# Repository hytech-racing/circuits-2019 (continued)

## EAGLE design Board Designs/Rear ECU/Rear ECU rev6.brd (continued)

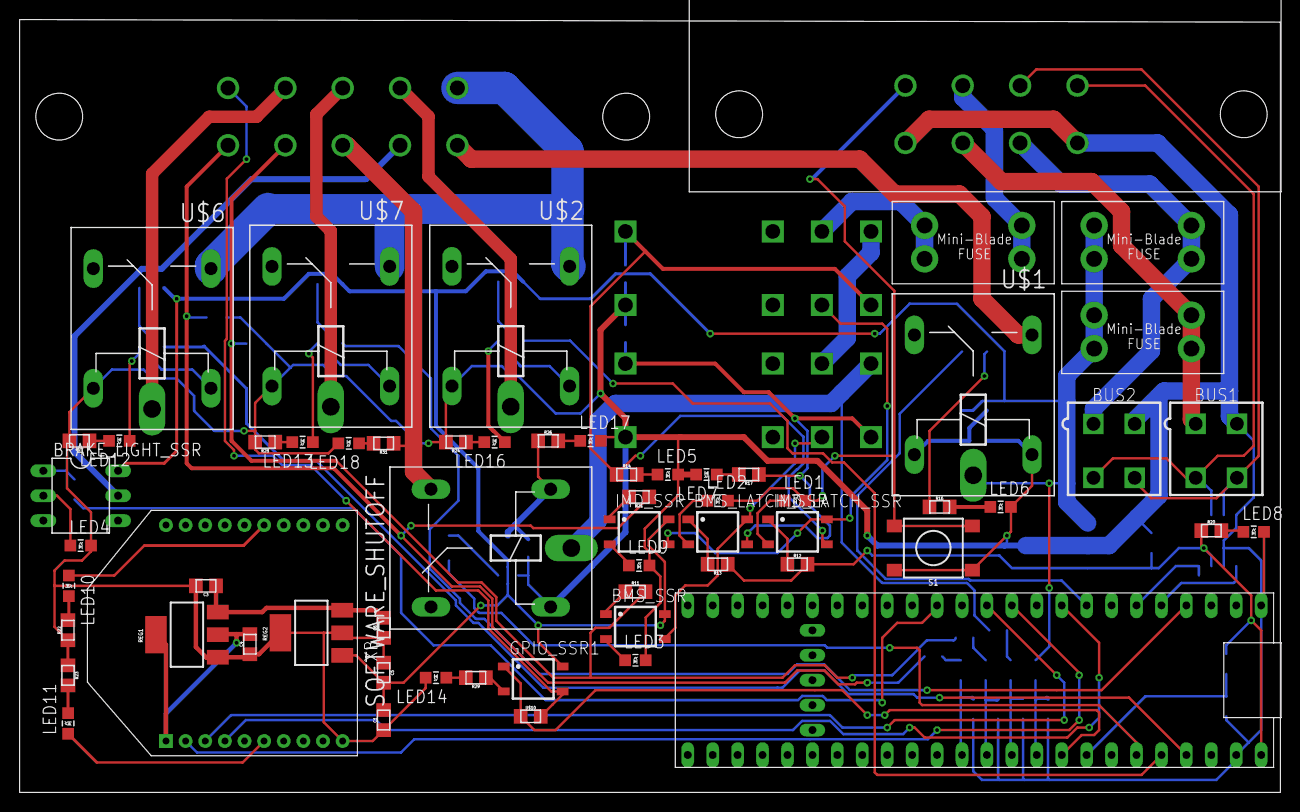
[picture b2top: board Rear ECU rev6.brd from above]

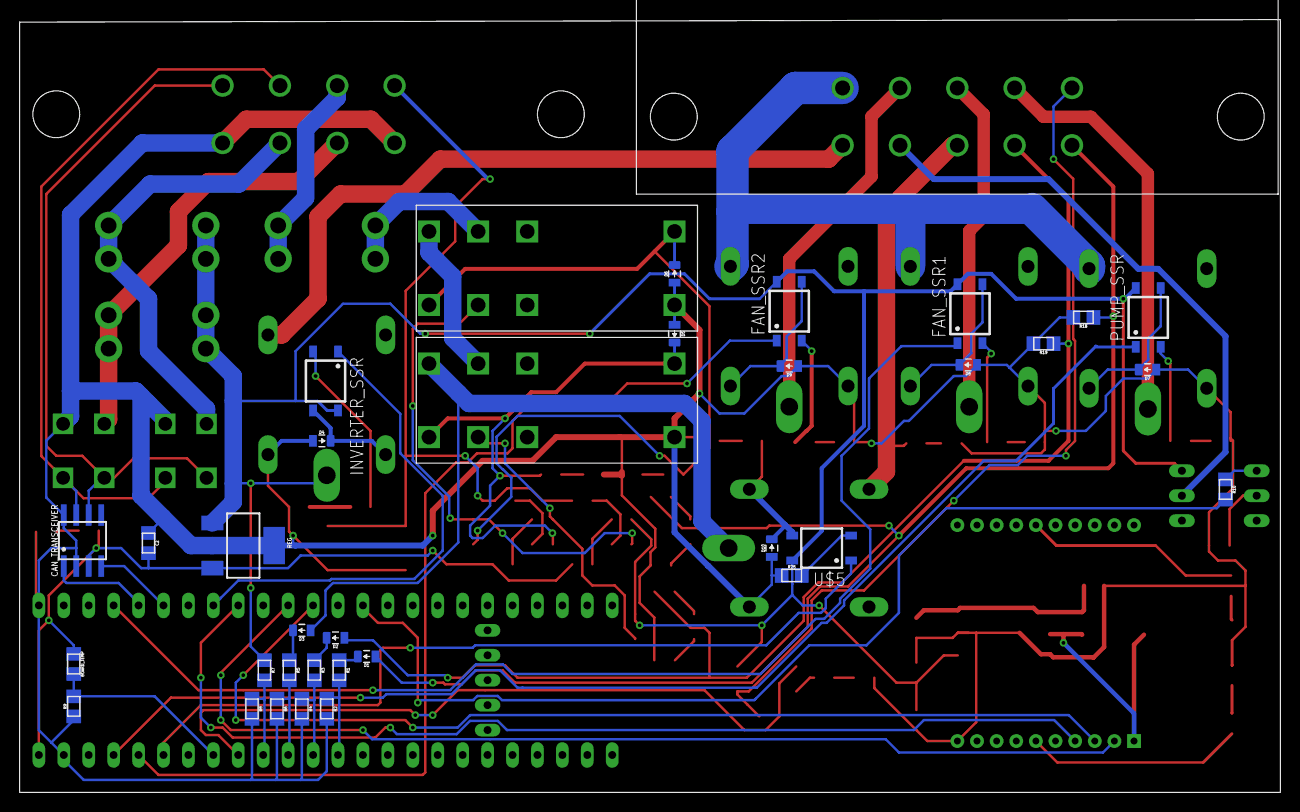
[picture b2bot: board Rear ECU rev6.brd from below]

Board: 2 copper layers, 128.4 x 78.7 mm, 96 parts (35 on the bottom side), 83 nets.

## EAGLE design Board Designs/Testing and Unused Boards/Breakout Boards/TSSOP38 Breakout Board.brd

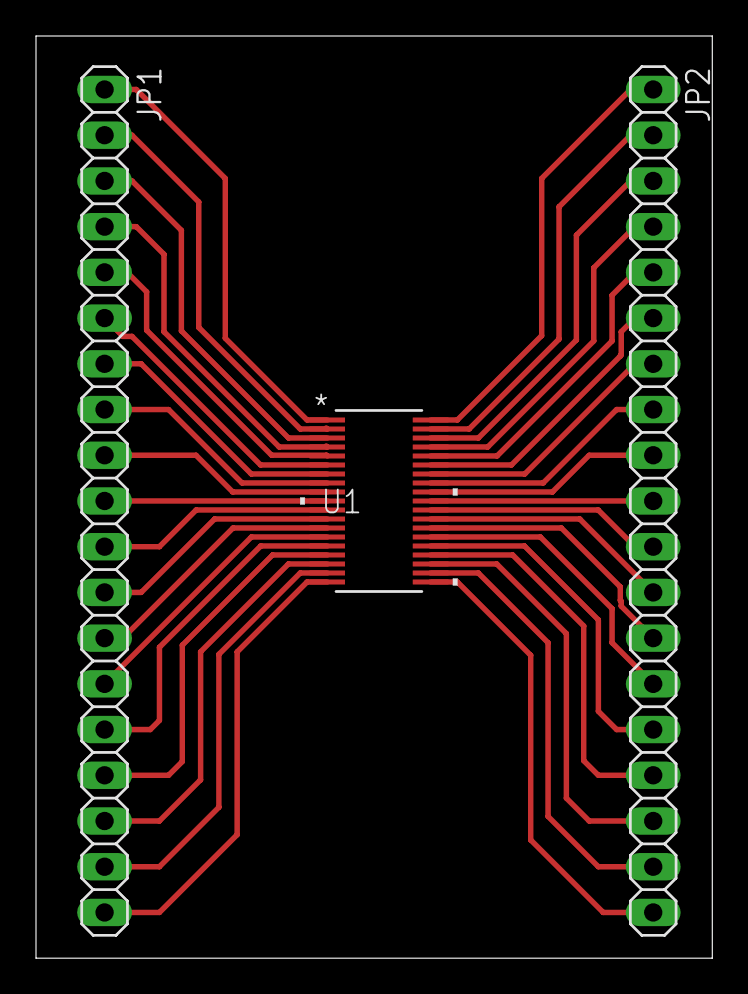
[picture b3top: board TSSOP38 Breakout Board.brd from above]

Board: 2 copper layers, 37.6 x 51.2 mm, 3 parts (0 on the bottom side), 38 nets.

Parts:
JP1, JP2: 1X19
U1: ADS7952SDBTDBT38-M; DBT38-M

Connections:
unnamed: JP1.1, U1.1
unnamed: JP1.2, U1.2
unnamed: JP1.3, U1.3
unnamed: JP1.4, U1.4
unnamed: JP1.5, U1.5
unnamed: JP1.6, U1.6
unnamed: JP1.7, U1.7
unnamed: JP1.8, U1.8
unnamed: JP1.19, U1.19
unnamed: JP1.18, U1.18
unnamed: JP1.17, U1.17
unnamed: JP1.16, U1.16
unnamed: JP1.15, U1.15
unnamed: JP1.14, U1.14
unnamed: JP1.13, U1.13
unnamed: JP1.12, U1.12
unnamed: JP1.11, U1.11
unnamed: JP1.10, U1.10
unnamed: JP1.9, U1.9
unnamed: JP2.1, U1.38
unnamed: JP2.2, U1.37
unnamed: JP2.3, U1.36
unnamed: JP2.4, U1.35
unnamed: JP2.5, U1.34
unnamed: JP2.6, U1.33
unnamed: JP2.7, U1.32
unnamed: JP2.8, U1.31
unnamed: JP2.9, U1.30
unnamed: JP2.10, U1.29
unnamed: JP2.11, U1.28
unnamed: JP2.12, U1.27
unnamed: JP2.13, U1.26
unnamed: JP2.14, U1.25
unnamed: JP2.15, U1.24
unnamed: JP2.16, U1.23
unnamed: JP2.17, U1.22
unnamed: JP2.18, U1.21
unnamed: JP2.19, U1.20

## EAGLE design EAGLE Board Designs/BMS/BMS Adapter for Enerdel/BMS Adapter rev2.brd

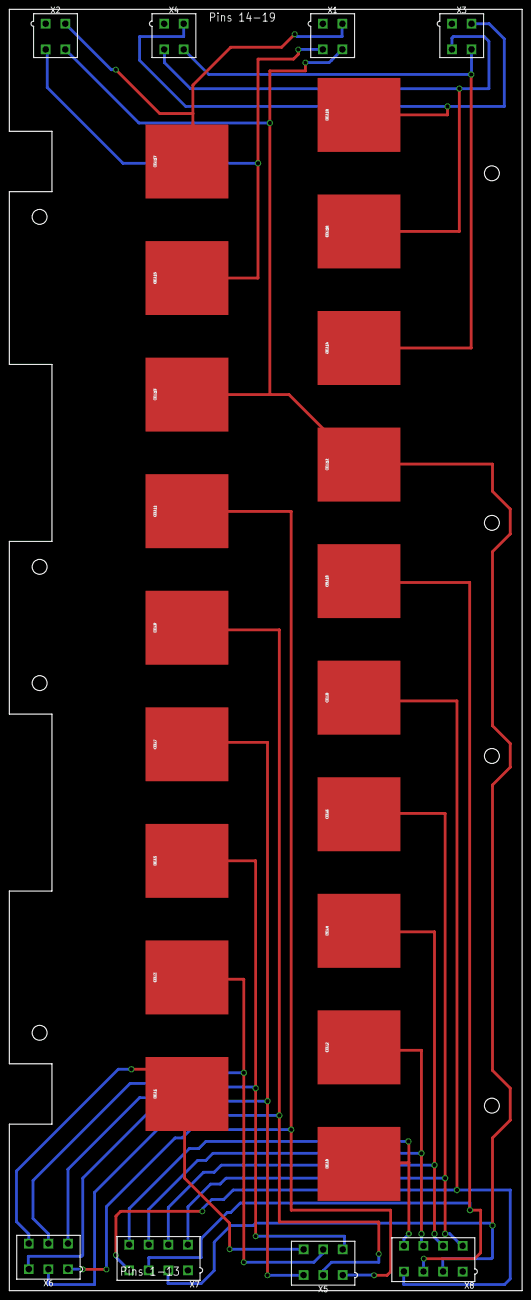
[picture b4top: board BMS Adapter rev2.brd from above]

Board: 2 copper layers, 110.0 x 274.8 mm, 27 parts (0 on the bottom side), 18 nets.

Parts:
CELL0, CELL1, CELL2, CELL3, CELL4, CELL5, CELL6, CELL7, CELL8, CELL9, CELL10, CELL11, CELL12, CELL13, CELL14, CELL15, CELL16, CELL17, CELL18: BATTERY_SPRING_KEYSTONE5222; KEYSTONE5222
X1, X2, X3, X4: CONNECTOR-4; MINIFIT_5566-4
X5, X6: CONNECTOR-6; MINIFIT_5566-6
X7, X8: CONNECTOR-8; MINIFIT_5566-8

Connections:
CELL0: CELL0.P$1, X7.8, X8.8
CELL1: CELL1.P$1, X5.6, X6.6
CELL2: CELL2.P$1, X7.7, X8.7
CELL3: CELL3.P$1, X5.5, X6.5
CELL4: CELL4.P$1, X7.6, X8.6
CELL5: CELL5.P$1, X5.4, X6.4
CELL6: CELL6.P$1, X7.5, X8.5
CELL7: CELL7.P$1, X5.3, X6.3
CELL8: CELL8.P$1, X7.4, X8.4
CELL9: CELL9.P$1, X5.2, X6.2
CELL10: CELL10.P$1, X7.3, X8.3
CELL11: CELL11.P$1, X5.1, X6.1
CELL12: CELL12.P$1, CELL13.P$1, X1.4, X2.4, X7.2, X8.2
CELL14: CELL14.P$1, X3.4, X4.4
CELL15: CELL15.P$1, X1.3, X2.3
CELL16: CELL16.P$1, X3.3, X4.3
CELL17: CELL17.P$1, X1.2, X2.2
CELL18: CELL18.P$1, X3.2, X4.2

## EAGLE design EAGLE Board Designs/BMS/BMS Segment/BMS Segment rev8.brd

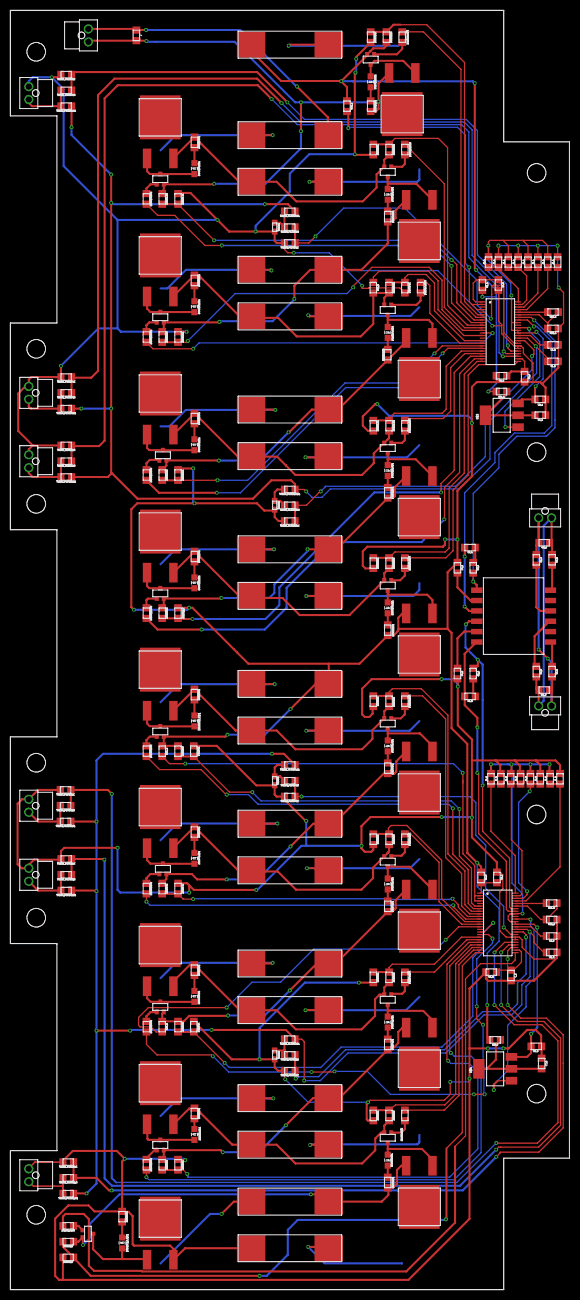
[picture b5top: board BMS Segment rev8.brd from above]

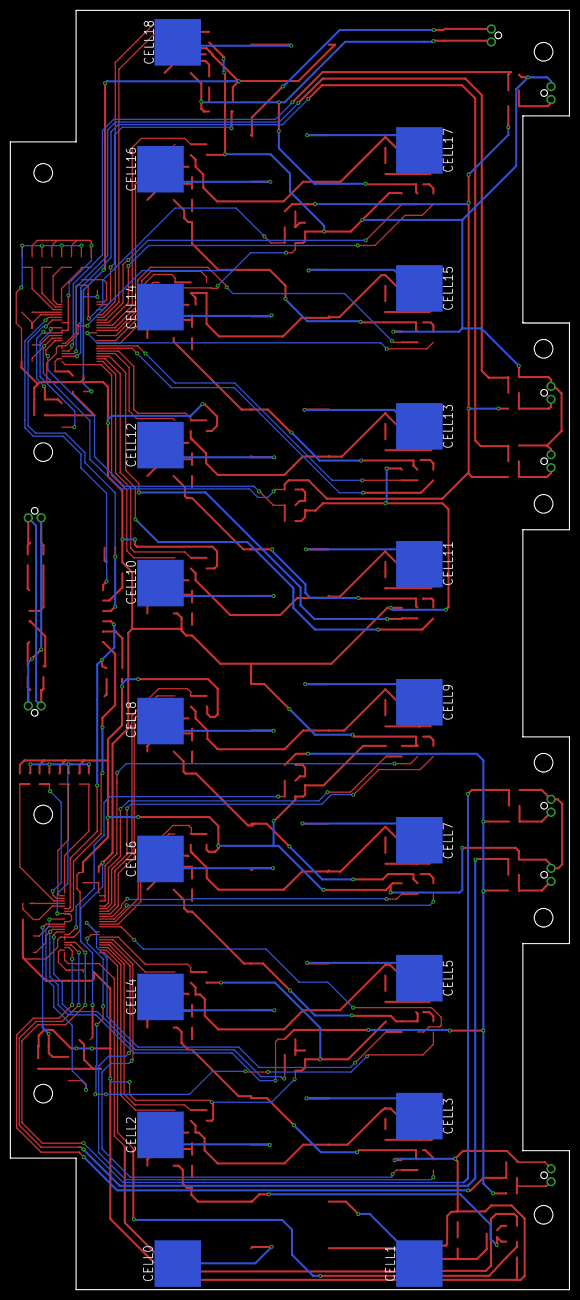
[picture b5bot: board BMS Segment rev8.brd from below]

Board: 2 copper layers, 108.0 x 247.1 mm, 267 parts (19 on the bottom side), 193 nets.

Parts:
AMS_TEST_PORT1: CONNECTOR-2NANO-FIT_VERTICAL-2; NANO-FIT_VERTICAL-2
C1_A, C1_B, C2_A, C2_B, C8_A, C8_B: 1uF; 0805
C3_A, C3_B: 15pF; 0805
C4_A, C4_B, C5_A: 10nF; 0805
C6_A, C6_B, C7_A, C7_B: 0.1uF; 0805
CELL0, CELL1, CELL2, CELL3, CELL4, CELL5, CELL6, CELL7, CELL8, CELL9, CELL10, CELL11, CELL12, CELL13, CELL14, CELL15, CELL16, CELL17, CELL18: BATTERY_SPRING; KEYSTONE5203
C_5: 10nF; 0805
DRAIN1:C, DRAIN2:C, DRAIN3:C, DRAIN4:C, DRAIN5:C, DRAIN6:C, DRAIN7:C, DRAIN8:C, DRAIN9:C, DRAIN10:C, DRAIN11:C, DRAIN12:C, DRAIN13:C, DRAIN14:C, DRAIN15:C, DRAIN16:C, DRAIN17:C, DRAIN18:C: 10nF; 0805
DRAIN1:DISCHARGE, DRAIN2:DISCHARGE, DRAIN3:DISCHARGE, DRAIN4:DISCHARGE, DRAIN5:DISCHARGE, DRAIN6:DISCHARGE, DRAIN7:DISCHARGE, DRAIN8:DISCHARGE, DRAIN9:DISCHARGE, DRAIN10:DISCHARGE, DRAIN11:DISCHARGE, DRAIN12:DISCHARGE, DRAIN13:DISCHARGE, DRAIN14:DISCHARGE, DRAIN15:DISCHARGE, DRAIN16:DISCHARGE, DRAIN17:DISCHARGE, DRAIN18:DISCHARGE: 5R; PWR163
DRAIN1:GATE, DRAIN2:GATE, DRAIN3:GATE, DRAIN4:GATE, DRAIN5:GATE, DRAIN6:GATE, DRAIN7:GATE, DRAIN8:GATE, DRAIN9:GATE, DRAIN10:GATE, DRAIN11:GATE, DRAIN12:GATE, DRAIN13:GATE, DRAIN14:GATE, DRAIN15:GATE, DRAIN16:GATE, DRAIN17:GATE, DRAIN18:GATE: 3K3; 0805
DRAIN1:LED1, DRAIN2:LED1, DRAIN3:LED1, DRAIN4:LED1, DRAIN5:LED1, DRAIN6:LED1, DRAIN7:LED1, DRAIN8:LED1, DRAIN9:LED1, DRAIN10:LED1, DRAIN11:LED1, DRAIN12:LED1, DRAIN13:LED1, DRAIN14:LED1, DRAIN15:LED1, DRAIN16:LED1, DRAIN17:LED1, DRAIN18:LED1: RED; LED-805
DRAIN1:PFET, DRAIN2:PFET, DRAIN3:PFET, DRAIN4:PFET, DRAIN5:PFET, DRAIN6:PFET, DRAIN7:PFET, DRAIN8:PFET, DRAIN9:PFET, DRAIN10:PFET, DRAIN11:PFET, DRAIN12:PFET, DRAIN13:PFET, DRAIN14:PFET, DRAIN15:PFET, DRAIN16:PFET, DRAIN17:PFET, DRAIN18:PFET: P-CHANNEL_MOSFET_DMP3099L-7; SOT23
DRAIN1:R, DRAIN2:R, DRAIN3:R, DRAIN4:R, DRAIN5:R, DRAIN6:R, DRAIN7:R, DRAIN8:R, DRAIN9:R, DRAIN10:R, DRAIN11:R, DRAIN12:R, DRAIN13:R, DRAIN14:R, DRAIN15:R, DRAIN16:R, DRAIN17:R, DRAIN18:R: 100R; 0805
DRAIN1:R1, DRAIN2:R1, DRAIN3:R1, DRAIN4:R1, DRAIN5:R1, DRAIN6:R1, DRAIN7:R1, DRAIN8:R1, DRAIN9:R1, DRAIN10:R1, DRAIN11:R1, DRAIN12:R1, DRAIN13:R1, DRAIN14:R1, DRAIN15:R1, DRAIN16:R1, DRAIN17:R1, DRAIN18:R1: 150R; 0805
F0, F1, F2, F3, F4, F5, F6, F7, F8, F9, F10, F11, F12, F13, F14, F15, F16, F17, F18: 0001.2704.11; 5X20MM_FUSE
ISOSPI_A: CONNECTOR-2NANO-FIT_VERTICAL-2; NANO-FIT_VERTICAL-2
ISOSPI_B: CONNECTOR-2NANO-FIT_VERTICAL-2; NANO-FIT_VERTICAL-2
J, J1_A, J1_B, J2_A, J2_B, J3_A, J3_B, J4_A, J4_B, J5_A, J5_B, J6_A, J6_B, J7_A, J7_B, J8_A, J8_B: 0805
R1_A, R1_B, R2_A, R2_B: 100R; 0805
R3_A, R3_B: 402R; 0805
R4_A, R4_B, R5_A, R5_B: 22R; 0805
RB1_A, RB1_B: 1K2; 0805
RB2_A, RB2_B: 800R; 0805
RIN_A: 100R; 0805
RIN_B: 100R; 0805
RM_A: 100R; 0805
RM_B: 100R; 0805
RU1_A, RU1_B: 100R; 0805
RU2_A, RU2_B: 100Ω; 0805
THERM1, THERM2, THERM3, THERM4: 10K; 0603
THERM1_A, THERM1_B, THERM2_A, THERM2_B, THERM3_A, THERM3_B: Th1; NANO-FIT_VERTICAL-2
THERM_FILTER1:C, THERM_FILTER2:C, THERM_FILTER3:C, THERM_FILTER4:C, THERM_FILTER5:C, THERM_FILTER6:C, THERM_FILTER7:C, THERM_FILTER8:C, THERM_FILTER9:C, THERM_FILTER10:C: 10nF; 0805
THERM_FILTER1:R, THERM_FILTER2:R, THERM_FILTER3:R, THERM_FILTER4:R, THERM_FILTER5:R, THERM_FILTER6:R, THERM_FILTER7:R, THERM_FILTER8:R, THERM_FILTER9:R, THERM_FILTER10:R: 100R; 0805
THERM_FILTER1:R1, THERM_FILTER2:R1, THERM_FILTER3:R1, THERM_FILTER4:R1, THERM_FILTER5:R1, THERM_FILTER6:R1, THERM_FILTER7:R1, THERM_FILTER8:R1, THERM_FILTER9:R1, THERM_FILTER10:R1: 10K; 0805
TRANSFORMER: HM2102NLT
U$1, U$2: LTC6804-2; LTC6804
U$3, U$4: SOT223

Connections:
C0_A: C5_A.1, R2_A.2, U$1.26
C0_B: C_5.1, R2_B.2, U$2.26
C1_A: DRAIN10:C.1, DRAIN10:R.2, U$1.24
C1_B: DRAIN1:C.1, DRAIN1:R.2, U$2.24
C2_A: DRAIN11:C.1, DRAIN11:R.2, U$1.22
C2_B: DRAIN2:C.1, DRAIN2:R.2, U$2.22
C3_A: DRAIN12:C.1, DRAIN12:R.2, U$1.20
C3_B: DRAIN3:C.1, DRAIN3:R.2, U$2.20
C4_A: DRAIN13:C.1, DRAIN13:R.2, U$1.18
C4_B: DRAIN4:C.1, DRAIN4:R.2, U$2.18
C5_A: DRAIN14:C.1, DRAIN14:R.2, U$1.16
C5_B: DRAIN5:C.1, DRAIN5:R.2, U$2.16
C7_A: DRAIN15:C.1, DRAIN15:R.2, U$1.12
C7_B: DRAIN6:C.1, DRAIN6:R.2, U$2.12
C8_A: DRAIN16:C.1, DRAIN16:R.2, U$1.10
C8_B: DRAIN7:C.1, DRAIN7:R.2, U$2.10
C9_A: DRAIN17:C.1, DRAIN17:R.2, U$1.8
C9_B: DRAIN8:C.1, DRAIN8:R.2, U$2.8
C10_A: DRAIN18:C.1, DRAIN18:R.2, U$1.6
C10_B: DRAIN9:C.1, DRAIN9:R.2, U$2.6
CC0: CELL0.P$1, F0.P$1
CC1: CELL1.P$1, F1.P$1
CC2: CELL2.P$1, F2.P$1
CC3: CELL3.P$1, F3.P$1
CC4: CELL4.P$1, F4.P$1
CC5: CELL5.P$1, F5.P$1
CC6: CELL6.P$1, F6.P$1
CC7: CELL7.P$1, F7.P$1
CC8: CELL8.P$1, F8.P$1
CC9: CELL9.P$1, F9.P$1
CC10: CELL10.P$1, F10.P$1
CC11: CELL11.P$1, F11.P$1
CC12: CELL12.P$1, F12.P$1
CC13: CELL13.P$1, F13.P$1
CC14: CELL14.P$1, F14.P$1
CC15: CELL15.P$1, F15.P$1
CC16: CELL16.P$1, F16.P$1
CC17: CELL17.P$1, F17.P$1
CC18: CELL18.P$1, F18.P$1
DRAIN1:GATE: DRAIN1:GATE.1, DRAIN1:PFET.1
DRAIN1:N$1: DRAIN1:DISCHARGE.1, DRAIN1:LED1.A, DRAIN1:PFET.3
DRAIN1:N$2: DRAIN1:LED1.C, DRAIN1:R1.2
DRAIN2:GATE: DRAIN2:GATE.1, DRAIN2:PFET.1
DRAIN2:N$1: DRAIN2:DISCHARGE.1, DRAIN2:LED1.A, DRAIN2:PFET.3
DRAIN2:N$2: DRAIN2:LED1.C, DRAIN2:R1.2
DRAIN3:GATE: DRAIN3:GATE.1, DRAIN3:PFET.1
DRAIN3:N$1: DRAIN3:DISCHARGE.1, DRAIN3:LED1.A, DRAIN3:PFET.3
DRAIN3:N$2: DRAIN3:LED1.C, DRAIN3:R1.2
DRAIN4:GATE: DRAIN4:GATE.1, DRAIN4:PFET.1
DRAIN4:N$1: DRAIN4:DISCHARGE.1, DRAIN4:LED1.A, DRAIN4:PFET.3
DRAIN4:N$2: DRAIN4:LED1.C, DRAIN4:R1.2
DRAIN5:GATE: DRAIN5:GATE.1, DRAIN5:PFET.1
DRAIN5:N$1: DRAIN5:DISCHARGE.1, DRAIN5:LED1.A, DRAIN5:PFET.3
DRAIN5:N$2: DRAIN5:LED1.C, DRAIN5:R1.2
DRAIN6:GATE: DRAIN6:GATE.1, DRAIN6:PFET.1
DRAIN6:N$1: DRAIN6:DISCHARGE.1, DRAIN6:LED1.A, DRAIN6:PFET.3
DRAIN6:N$2: DRAIN6:LED1.C, DRAIN6:R1.2
DRAIN7:GATE: DRAIN7:GATE.1, DRAIN7:PFET.1
DRAIN7:N$1: DRAIN7:DISCHARGE.1, DRAIN7:LED1.A, DRAIN7:PFET.3
DRAIN7:N$2: DRAIN7:LED1.C, DRAIN7:R1.2
DRAIN8:GATE: DRAIN8:GATE.1, DRAIN8:PFET.1
DRAIN8:N$1: DRAIN8:DISCHARGE.1, DRAIN8:LED1.A, DRAIN8:PFET.3
DRAIN8:N$2: DRAIN8:LED1.C, DRAIN8:R1.2
DRAIN9:GATE: DRAIN9:GATE.1, DRAIN9:PFET.1
DRAIN9:N$1: DRAIN9:DISCHARGE.1, DRAIN9:LED1.A, DRAIN9:PFET.3
DRAIN9:N$2: DRAIN9:LED1.C, DRAIN9:R1.2
DRAIN10:GATE: DRAIN10:GATE.1, DRAIN10:PFET.1
DRAIN10:N$1: DRAIN10:DISCHARGE.1, DRAIN10:LED1.A, DRAIN10:PFET.3
DRAIN10:N$2: DRAIN10:LED1.C, DRAIN10:R1.2
DRAIN11:GATE: DRAIN11:GATE.1, DRAIN11:PFET.1
DRAIN11:N$1: DRAIN11:DISCHARGE.1, DRAIN11:LED1.A, DRAIN11:PFET.3
DRAIN11:N$2: DRAIN11:LED1.C, DRAIN11:R1.2
DRAIN12:GATE: DRAIN12:GATE.1, DRAIN12:PFET.1
DRAIN12:N$1: DRAIN12:DISCHARGE.1, DRAIN12:LED1.A, DRAIN12:PFET.3
DRAIN12:N$2: DRAIN12:LED1.C, DRAIN12:R1.2
DRAIN13:GATE: DRAIN13:GATE.1, DRAIN13:PFET.1
DRAIN13:N$1: DRAIN13:DISCHARGE.1, DRAIN13:LED1.A, DRAIN13:PFET.3
DRAIN13:N$2: DRAIN13:LED1.C, DRAIN13:R1.2
DRAIN14:GATE: DRAIN14:GATE.1, DRAIN14:PFET.1
DRAIN14:N$1: DRAIN14:DISCHARGE.1, DRAIN14:LED1.A, DRAIN14:PFET.3
DRAIN14:N$2: DRAIN14:LED1.C, DRAIN14:R1.2
DRAIN15:GATE: DRAIN15:GATE.1, DRAIN15:PFET.1
DRAIN15:N$1: DRAIN15:DISCHARGE.1, DRAIN15:LED1.A, DRAIN15:PFET.3
DRAIN15:N$2: DRAIN15:LED1.C, DRAIN15:R1.2
DRAIN16:GATE: DRAIN16:GATE.1, DRAIN16:PFET.1
DRAIN16:N$1: DRAIN16:DISCHARGE.1, DRAIN16:LED1.A, DRAIN16:PFET.3
DRAIN16:N$2: DRAIN16:LED1.C, DRAIN16:R1.2
DRAIN17:GATE: DRAIN17:GATE.1, DRAIN17:PFET.1
DRAIN17:N$1: DRAIN17:DISCHARGE.1, DRAIN17:LED1.A, DRAIN17:PFET.3
DRAIN17:N$2: DRAIN17:LED1.C, DRAIN17:R1.2
DRAIN18:GATE: DRAIN18:GATE.1, DRAIN18:PFET.1
DRAIN18:N$1: DRAIN18:DISCHARGE.1, DRAIN18:LED1.A, DRAIN18:PFET.3
DRAIN18:N$2: DRAIN18:LED1.C, DRAIN18:R1.2
DRIVE_A: U$1.38, U$3.1
DRIVE_B: U$2.38, U$4.1
GPIO1_A: THERM_FILTER6:C.1, THERM_FILTER6:R.1, U$1.27
GPIO1_B: THERM_FILTER1:C.1, THERM_FILTER1:R.1, U$2.27
GPIO2_A: THERM_FILTER7:C.1, THERM_FILTER7:R.1, U$1.28
GPIO2_B: THERM_FILTER2:C.1, THERM_FILTER2:R.1, U$2.28
GPIO3_A: THERM_FILTER8:C.1, THERM_FILTER8:R.1, U$1.29
GPIO3_B: THERM_FILTER3:C.1, THERM_FILTER3:R.1, U$2.29
GPIO4_A: THERM_FILTER9:C.1, THERM_FILTER9:R.1, U$1.32
GPIO4_B: THERM_FILTER4:C.1, THERM_FILTER4:R.1, U$2.32
GPIO5_A: THERM_FILTER10:C.1, THERM_FILTER10:R.1, U$1.33
GPIO5_B: THERM_FILTER5:C.1, THERM_FILTER5:R.1, U$2.33
IM_A: C3_A.2, TRANSFORMER.P$9, U$1.41
IM_B: C3_B.2, TRANSFORMER.P$12, U$2.41
IP_A: R3_A.1, TRANSFORMER.P$7, U$1.42
IP_B: R3_B.1, TRANSFORMER.P$10, U$2.42
ISOSPI-M: ISOSPI_A.P$2, ISOSPI_B.P$2, R5_A.2, R5_B.2, RM_A.2, RM_B.2
ISOSPI-P: ISOSPI_A.P$1, ISOSPI_B.P$1, R4_A.2, R4_B.2, RM_A.1, RM_B.1
unnamed: C4_B.1, TRANSFORMER.P$11
unnamed: RB1_B.2, U$2.44
unnamed: THERM1_B.P$1, THERM_FILTER1:R.2, THERM_FILTER1:R1.2
unnamed: RB1_B.1, RB2_B.2, U$2.43
unnamed: R4_B.1, TRANSFORMER.P$3
unnamed: RB1_A.2, U$1.44
unnamed: R5_B.1, TRANSFORMER.P$1
unnamed: J7_B.1, J8_B.1, U$2.48
unnamed: J5_B.1, J6_B.1, U$2.47
unnamed: C3_B.1, R3_B.2
unnamed: J3_B.1, J4_B.1, U$2.46
unnamed: J1_B.1, J2_B.1, U$2.45
unnamed: THERM4.2, THERM_FILTER5:R.2, THERM_FILTER5:R1.2
unnamed: THERM2_B.P$1, THERM_FILTER2:R.2, THERM_FILTER2:R1.2
unnamed: THERM3.2, THERM_FILTER4:R.2, THERM_FILTER4:R1.2
unnamed: RB1_A.1, RB2_A.2, U$1.43
unnamed: C4_A.1, TRANSFORMER.P$8
unnamed: R4_A.1, TRANSFORMER.P$6
unnamed: R5_A.1, TRANSFORMER.P$4
unnamed: C3_A.1, R3_A.2
unnamed: THERM3_B.P$1, THERM_FILTER3:R.2, THERM_FILTER3:R1.2
unnamed: J7_A.1, J8_A.1, U$1.48
unnamed: J5_A.1, J6_A.1, U$1.47
unnamed: J3_A.1, J4_A.1, U$1.46
unnamed: J1_A.1, J2_A.1, U$1.45
unnamed: THERM1.2, THERM_FILTER9:R.2, THERM_FILTER9:R1.2
unnamed: THERM3_A.P$1, THERM_FILTER8:R.2, THERM_FILTER8:R1.2
unnamed: THERM2.2, THERM_FILTER10:R.2, THERM_FILTER10:R1.2
unnamed: THERM2_A.P$1, THERM_FILTER7:R.2, THERM_FILTER7:R1.2
unnamed: THERM1_A.P$1, THERM_FILTER6:R.2, THERM_FILTER6:R1.2
S1_A: DRAIN10:GATE.2, U$1.25
S1_B: DRAIN1:GATE.2, U$2.25
S2_A: DRAIN11:GATE.2, U$1.23
S2_B: DRAIN2:GATE.2, U$2.23
S3_A: DRAIN12:GATE.2, U$1.21
S3_B: DRAIN3:GATE.2, U$2.21
S4_A: DRAIN13:GATE.2, U$1.19
S4_B: DRAIN4:GATE.2, U$2.19
S5_A: DRAIN14:GATE.2, U$1.17
S5_B: DRAIN5:GATE.2, U$2.17
S7_A: DRAIN15:GATE.2, U$1.13
S7_B: DRAIN6:GATE.2, U$2.13
S8_A: DRAIN16:GATE.2, U$1.11
S8_B: DRAIN7:GATE.2, U$2.11
S9_A: DRAIN17:GATE.2, U$1.9
S9_B: DRAIN8:GATE.2, U$2.9
S10_A: DRAIN18:GATE.2, U$1.7
S10_B: DRAIN9:GATE.2, U$2.7
SENSE1: DRAIN1:PFET.2, DRAIN1:R.1, DRAIN2:DISCHARGE.2, DRAIN2:R1.1, F1.P$2
SENSE2: DRAIN2:PFET.2, DRAIN2:R.1, DRAIN3:DISCHARGE.2, DRAIN3:R1.1, F2.P$2
SENSE3: DRAIN3:PFET.2, DRAIN3:R.1, DRAIN4:DISCHARGE.2, DRAIN4:R1.1, F3.P$2
SENSE4: DRAIN4:PFET.2, DRAIN4:R.1, DRAIN5:DISCHARGE.2, DRAIN5:R1.1, F4.P$2
SENSE5: DRAIN5:PFET.2, DRAIN5:R.1, DRAIN6:DISCHARGE.2, DRAIN6:R1.1, F5.P$2, RU2_B.1
SENSE6: DRAIN6:PFET.2, DRAIN6:R.1, DRAIN7:DISCHARGE.2, DRAIN7:R1.1, F6.P$2
SENSE7: DRAIN7:PFET.2, DRAIN7:R.1, DRAIN8:DISCHARGE.2, DRAIN8:R1.1, F7.P$2
SENSE8: DRAIN8:PFET.2, DRAIN8:R.1, DRAIN9:DISCHARGE.2, DRAIN9:R1.1, F8.P$2
SENSE10: DRAIN10:PFET.2, DRAIN10:R.1, DRAIN11:DISCHARGE.2, DRAIN11:R1.1, F10.P$2
SENSE11: DRAIN11:PFET.2, DRAIN11:R.1, DRAIN12:DISCHARGE.2, DRAIN12:R1.1, F11.P$2
SENSE12: DRAIN12:PFET.2, DRAIN12:R.1, DRAIN13:DISCHARGE.2, DRAIN13:R1.1, F12.P$2
SENSE13: DRAIN13:PFET.2, DRAIN13:R.1, DRAIN14:DISCHARGE.2, DRAIN14:R1.1, F13.P$2
SENSE14: DRAIN14:PFET.2, DRAIN14:R.1, DRAIN15:DISCHARGE.2, DRAIN15:R1.1, F14.P$2, RU2_A.1
SENSE15: DRAIN15:PFET.2, DRAIN15:R.1, DRAIN16:DISCHARGE.2, DRAIN16:R1.1, F15.P$2
SENSE16: DRAIN16:PFET.2, DRAIN16:R.1, DRAIN17:DISCHARGE.2, DRAIN17:R1.1, F16.P$2
SENSE17: AMS_TEST_PORT1.P$2, DRAIN17:PFET.2, DRAIN17:R.1, DRAIN18:DISCHARGE.2, DRAIN18:R1.1, J.2
SENSE17_J: AMS_TEST_PORT1.P$1, F17.P$2, J.1
SENSE18: DRAIN18:PFET.2, DRAIN18:R.1, F18.P$2, R1_A.1, RIN_A.1, RU1_A.1
UNUSED1_A: RU1_A.2, U$1.2, U$1.4
UNUSED1_B: RU1_B.2, U$2.2, U$2.4
UNUSED2_A: RU2_A.2, U$1.14
UNUSED2_B: RU2_B.2, U$2.14
V+_A: C6_A.1, R1_A.2, U$1.1
V+_B: C6_B.1, R1_B.2, U$2.1
V-_A: C1_A.2, C2_A.2, C4_A.2, C5_A.2, C6_A.2, C7_A.2, C8_A.2, DRAIN9:PFET.2, DRAIN9:R.1, DRAIN10:C.2, DRAIN10:DISCHARGE.2, DRAIN10:R1.1, DRAIN11:C.2, DRAIN12:C.2, DRAIN13:C.2, DRAIN14:C.2, DRAIN15:C.2, DRAIN16:C.2, DRAIN17:C.2, DRAIN18:C.2, F9.P$2, J1_A.2, J3_A.2, J5_A.2, J7_A.2, R1_B.1, R2_A.1, RB2_A.1, RIN_B.1, RU1_B.1, THERM1.1, THERM1_A.P$2, THERM2.1, THERM2_A.P$2, THERM3_A.P$2, THERM_FILTER6:C.2, THERM_FILTER7:C.2, THERM_FILTER8:C.2, THERM_FILTER9:C.2, THERM_FILTER10:C.2, U$1.30, U$1.31
V-_B: C1_B.2, C2_B.2, C4_B.2, C6_B.2, C7_B.2, C8_B.2, C_5.2, DRAIN1:C.2, DRAIN1:DISCHARGE.2, DRAIN1:R1.1, DRAIN2:C.2, DRAIN3:C.2, DRAIN4:C.2, DRAIN5:C.2, DRAIN6:C.2, DRAIN7:C.2, DRAIN8:C.2, DRAIN9:C.2, F0.P$2, J1_B.2, J3_B.2, J5_B.2, J7_B.2, R2_B.1, RB2_B.1, THERM1_B.P$2, THERM2_B.P$2, THERM3.1, THERM3_B.P$2, THERM4.1, THERM_FILTER1:C.2, THERM_FILTER2:C.2, THERM_FILTER3:C.2, THERM_FILTER4:C.2, THERM_FILTER5:C.2, U$2.30, U$2.31
VIN_A: C7_A.1, RIN_A.2, U$3.2, U$3.4
VIN_B: C7_B.1, RIN_B.2, U$4.2, U$4.4
VREF1_A: C2_A.1, U$1.35
VREF1_B: C2_B.1, U$2.35
VREF2_A: C1_A.1, THERM_FILTER6:R1.1, THERM_FILTER7:R1.1, THERM_FILTER8:R1.1, THERM_FILTER9:R1.1, THERM_FILTER10:R1.1, U$1.34
VREF2_B: C1_B.1, THERM_FILTER1:R1.1, THERM_FILTER2:R1.1, THERM_FILTER3:R1.1, THERM_FILTER4:R1.1, THERM_FILTER5:R1.1, U$2.34
VREG_A: C8_A.1, J2_A.2, J4_A.2, J6_A.2, J8_A.2, U$1.36, U$1.37, U$1.40, U$3.3
VREG_B: C8_B.1, J2_B.2, J4_B.2, J6_B.2, J8_B.2, U$2.36, U$2.37, U$2.40, U$4.3

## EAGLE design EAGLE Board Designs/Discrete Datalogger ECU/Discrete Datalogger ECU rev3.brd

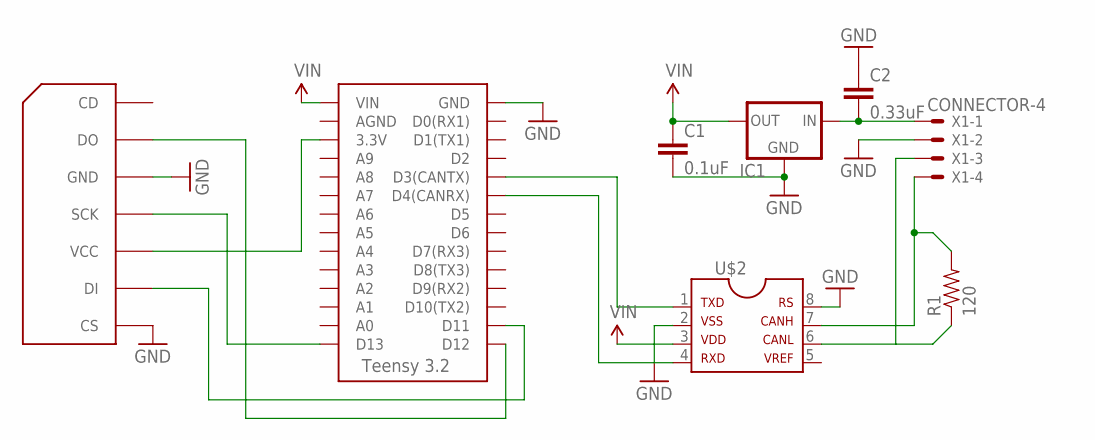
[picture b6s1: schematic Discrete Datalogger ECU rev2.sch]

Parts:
C1: 0.1uF; CAP-PTH-SMALL
C2: 0.33uF; CAP-PTH-SMALL
IC1: 5VREG_L7805_VERT; TO-220
R1: 120; AXIAL-0.3
U$1: TEENSY_3.2_SIMPLE
U$2: MCP2551DIL; DIL08
U$3: SDCARD_INTERFACE
X1: CONNECTOR-4; MINIFIT_5566-4

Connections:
12V: C2.2, IC1.1 (IN), X1.1
CANH: R1.P$2 (2), U$2.7, X1.4
CANL: R1.P$1 (1), U$2.6, X1.3
GND: C1.2, C2.1, IC1.2 (GND), U$1.GND, U$2.2, U$2.8, U$3.CS, U$3.GND, X1.2
unnamed 4: U$1.VBAT; also elsewhere on the board
unnamed 5: U$1.GND2; also elsewhere on the board
unnamed: U$1.D3(CANTX), U$2.1
unnamed: U$1.D4(CANRX), U$2.4
unnamed: U$1.D13, U$3.SCK
unnamed: U$1.D11, U$3.DI
unnamed: U$1.3.3V, U$3.VCC
unnamed: U$1.D12, U$3.DO
VIN: C1.1, IC1.3 (OUT), U$1.VIN, U$2.3

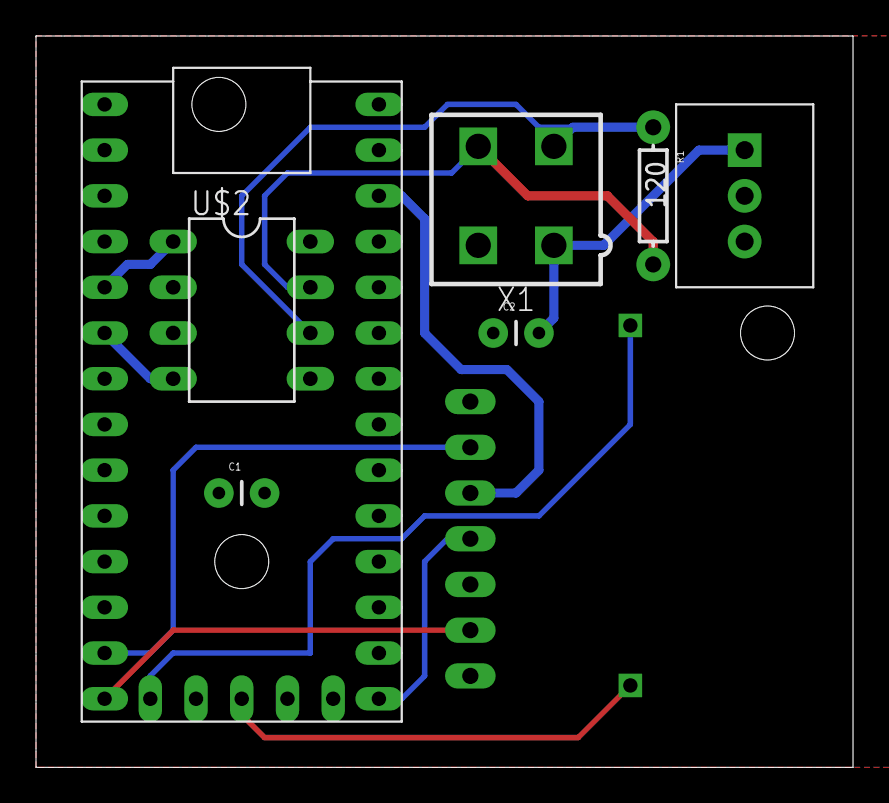
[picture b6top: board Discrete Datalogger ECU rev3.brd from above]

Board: 2 copper layers, 45.4 x 40.6 mm, 9 parts (1 on the bottom side), 13 nets.

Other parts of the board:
U$4: COIN-CELL-HOLDER

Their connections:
unnamed 4: U$4.VDD; also elsewhere on the board
unnamed 5: U$4.GND; also elsewhere on the board

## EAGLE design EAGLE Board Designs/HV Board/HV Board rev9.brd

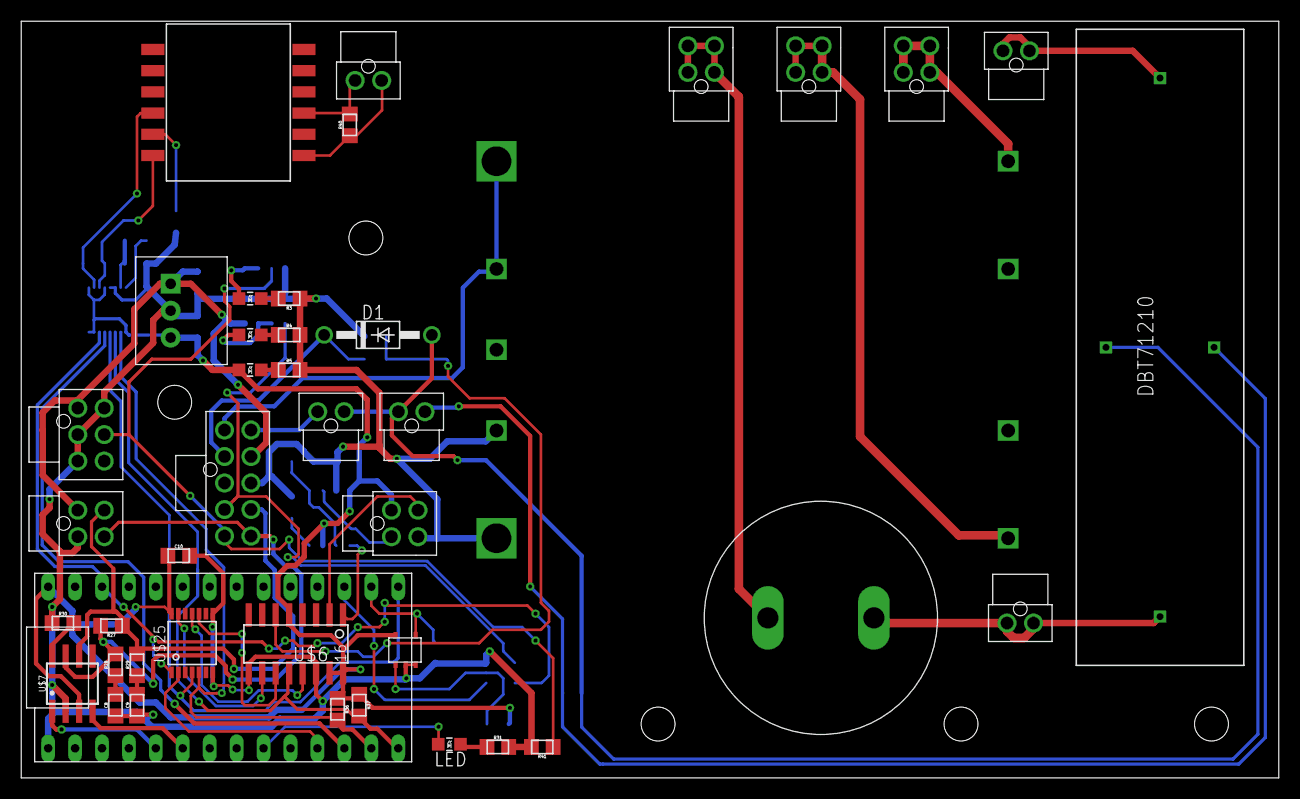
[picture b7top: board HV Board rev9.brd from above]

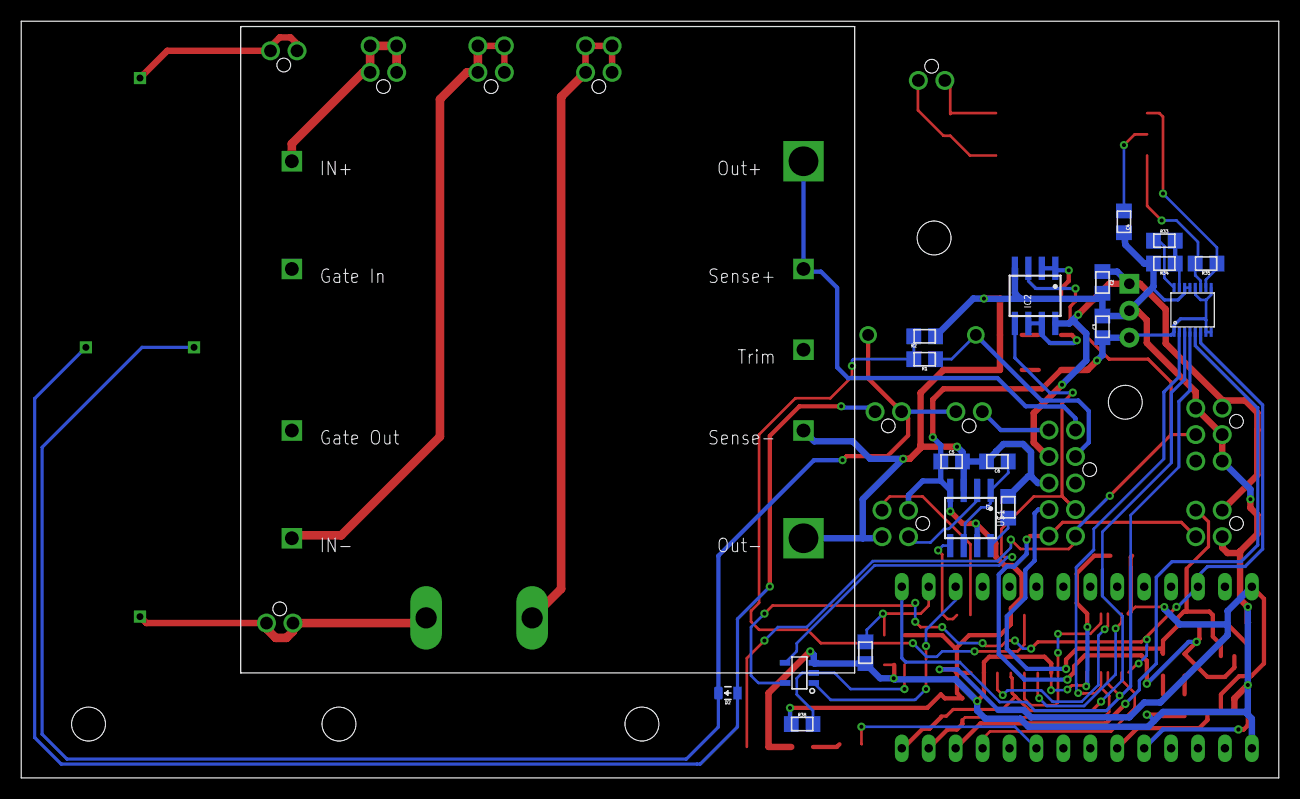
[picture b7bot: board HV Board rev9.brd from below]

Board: 2 copper layers, 118.6 x 71.4 mm, 60 parts (19 on the bottom side), 54 nets.

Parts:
BMS-OK: GREEN; LED-805
C1: 180µF; LLS2V221MELZ
C2, C3: 10uF; 0805
C4: 27pF; 0805
C5, C6, C10: 0.1uF; 0805
C7: 530pF; 0805
C8, C9: 560pF; 0805
CURRENT: CURRENT; NANO-FIT_VERTICAL-4
D1: DIODE; DO-41
D2: DIODE0805; 0805_D
DISCH+: DISCHARGE+; NANO-FIT_VERTICAL-2
HV+FUSED_1A-IMD+: HV+; NANO-FIT_VERTICAL-4
HV+UNFUSED: HV+UNFUSED; NANO-FIT_VERTICAL-2
HV-FUSED_1A-IMD-: HV-; NANO-FIT_VERTICAL-4
HV-UNFUSED_DISCHARGE-: HV-UNFUSED; NANO-FIT_VERTICAL-4
IC1: OKI-78SR
IC2: NE5532SOIC; SOIC-08
IMD: CONNECTOR-6NANO-FIT_VERTICAL-6; NANO-FIT_VERTICAL-6
IMD-OK: YELLOW; LED-805
INTERLOCK: INTERLOCK; NANO-FIT_VERTICAL-2
ISO_SPI: ISO_SPI; NANO-FIT_VERTICAL-2
LED: BLUE; LED-805
MAIN: MAIN; NANO-FIT_VERTICAL-10
ON-LED: PURPLE; LED-805
POWER: POWER; NANO-FIT_VERTICAL-4
R1: 43k; 0805
R2: 12k; 0805
R3, R4: 820; 0805
R5: 270; 0805
R27, R35: 120; 0805
R28, R29, R40: 100; 0805
R30, R33, R34: 1k; 0805
R31: 43; 0805
R36, R37, R41: 2k; 0805
R38: 430; 0805
R42: 10k; 0805
RELAYS: RELAYS; NANO-FIT_VERTICAL-2
U$1: SOIC-08
U$2: HM2102NLT
U$3: SN74LVC1G08; SOT-23-5
U$4: DBT71210
U$5: HV_DCDC_VI-J71-CZ
U$6: MCP3208SOIC; SOIC-16
U$7: MCP2551; SOIC-08
U$8: LTC6820; MSOP-16
U$9: TEENSY_3.2_SIMPLE
U$10: STWD100; SOT23-5
U$25: TXB0104TSSOP; TSSOP-14

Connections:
+3V3: U$3.5, U$8.6, U$9.3.3V, U$25.1
+5V: C3.1, C5.1, C10.1, CURRENT.P$1, IC1.3, ON-LED.A, R36.1, R37.1, R38.1, U$1.4, U$1.7, U$6.5, U$6.15, U$6.16, U$7.3, U$8.1, U$8.7, U$8.8, U$8.9, U$8.12, U$9.VIN, U$10.VCC, U$25.14
+12V: C2.1, IC1.1, IC2.8, IMD.P$1, MAIN.P$7, POWER.P$1
BMS_OK: IC2.5, MAIN.P$4, U$3.4
CANH: MAIN.P$10, POWER.P$4, R27.2, R28.2, U$7.7
CANL: MAIN.P$9, POWER.P$3, R27.1, R29.2, U$7.6
CS_LTC6820: U$8.5, U$9.D10(TX2)
CS_MCP3208_3.3V: U$9.D9(RX2), U$25.2
CUR_SENSE: CURRENT.P$2, U$1.2
DISCHARGE_RELAY_GND: D2.A, RELAYS.P$2, U$4.COIL-
GND: C2.2, C3.2, C4.2, C5.2, C6.2, C7.2, C8.1, C9.1, C10.2, CURRENT.P$4, IC1.2, IC2.4, IMD.P$2, IMD.P$3, IMD.P$4, MAIN.P$8, POWER.P$2, R2.1, R3.1, R4.2, R5.2, R30.1, R31.2, R34.2, R41.2, R42.2, U$1.3, U$3.3, U$5.8SENSE-, U$5.9VOUT-, U$6.9, U$6.14, U$7.2, U$8.13, U$8.14, U$9.GND, U$10.EN, U$10.GND, U$25.7, U$25.8
HV+FUSED_1A: HV+FUSED_1A-IMD+.P$1, HV+FUSED_1A-IMD+.P$2, HV+FUSED_1A-IMD+.P$3, HV+FUSED_1A-IMD+.P$4, U$5.1VIN+
HV+UNFUSED: C1.P$1, HV+UNFUSED.P$1, HV+UNFUSED.P$2, U$4.CONTACT1
HV+UNFUSED_FSAE_DISCHARGE: DISCH+.P$1, DISCH+.P$2, U$4.CONTACT2
HV-FUSED_1A: HV-FUSED_1A-IMD-.P$1, HV-FUSED_1A-IMD-.P$2, HV-FUSED_1A-IMD-.P$3, HV-FUSED_1A-IMD-.P$4, U$5.4VIN-
HV-UNFUSED: C1.P$2, HV-UNFUSED_DISCHARGE-.P$1, HV-UNFUSED_DISCHARGE-.P$2, HV-UNFUSED_DISCHARGE-.P$3, HV-UNFUSED_DISCHARGE-.P$4
IM: R35.1, U$2.P$10, U$8.10
IP: R35.2, U$2.P$12, U$8.11
ISOSPI-M: ISO_SPI.P$2, R40.2, U$2.P$3
ISOSPI-P: ISO_SPI.P$1, R40.1, U$2.P$1
MISO: R37.2, U$6.12, U$8.3, U$9.D12
MOSI_5V: U$6.11, U$25.10
MOSI_TEENSY: R36.2, U$8.2, U$9.D11, U$25.5
unnamed: U$1.5, U$6.1
unnamed: C6.1, U$1.1, U$1.6
unnamed: ON-LED.C, R5.1
unnamed: C7.1, U$1.8
unnamed: U$6.10, U$25.13
unnamed: R1.2, R2.2, U$6.6
unnamed: U$7.1, U$9.D3(CANTX)
unnamed: R30.2, U$7.8
unnamed: C8.2, R28.1
unnamed: C9.2, R29.1
unnamed: LED.C, R31.1
unnamed: R33.1, U$8.16
unnamed: R33.2, R34.1, U$8.15
unnamed: C4.1, U$2.P$11
unnamed: U$7.4, U$9.D4(CANRX)
unnamed: LED.A, U$9.D7(RX3)
unnamed: R38.2, U$3.2, U$10.WDO
unnamed: U$3.1, U$9.A1
unnamed: IC2.1, IC2.2, IMD-OK.A
unnamed: BMS-OK.A, IC2.6, IC2.7
unnamed: BMS-OK.C, R4.1
unnamed: IMD-OK.C, R3.2
unnamed: R42.1, U$9.A0, U$10.WDI
OKHS: IC2.3, IMD.P$5, MAIN.P$5, R41.1
SCK_5V: U$6.13, U$25.11
SCK_TEENSY: U$8.4, U$9.D13, U$25.4
SHUTDOWN6: INTERLOCK.P$1, MAIN.P$6
SHUTDOWN7: D1.A, D2.C, INTERLOCK.P$2, RELAYS.P$1, U$4.COIL+
SHUTDOWN7_EXT_OUT: D1.C, MAIN.P$2, R1.1
TEMP_SENSE: CURRENT.P$3, U$6.2
TSAL+: MAIN.P$1, U$5.5VOUT+, U$5.6SENSE+
